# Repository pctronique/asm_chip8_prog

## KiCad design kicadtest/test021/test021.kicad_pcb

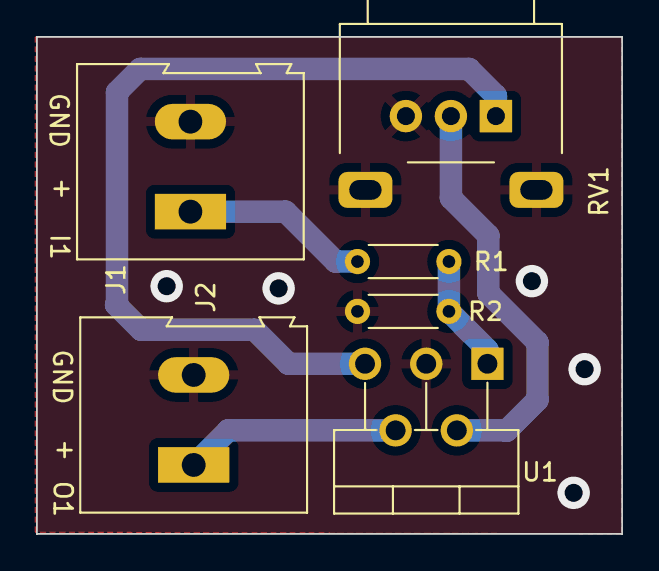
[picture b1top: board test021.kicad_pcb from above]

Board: 2 copper layers, 32.5 x 27.6 mm, 6 parts (0 on the bottom side), 5 nets.

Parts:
J1, J2: TerminalBlock_Altech_AK300-2_P5.00mm
R1, R2: 100k; R_Axial_DIN0204_L3.6mm_D1.6mm_P5.08mm_Horizontal
RV1: 100k; Potentiometer_Alps_RK09L_Single_Horizontal
U1: TO-220-5_P3.4x3.7mm_StaggerOdd_Lead3.8mm_Vertical

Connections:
V1: J1.1, R1.1, RV1.1, U1.5 (V+)
V2: R1.2, R2.1, U1.1 (+)
V3: RV1.2, U1.2 (-)
V4: J2.1, U1.4
VGND: J1.2, J2.2, R2.2, RV1.3, RV1.MP, U1.3 (V-)

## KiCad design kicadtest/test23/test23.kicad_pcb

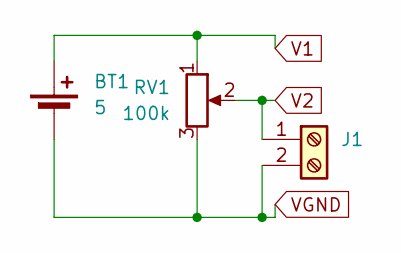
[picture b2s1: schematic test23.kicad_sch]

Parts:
BT1: 5; BatteryHolder_Keystone_103_1x20mm
J1: TerminalBlock_Altech_AK300-2_P5.00mm
RV1: 100k; Potentiometer_Alps_RK09K_Single_Vertical

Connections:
V1: BT1.1 (+), RV1.1
V2: J1.1, RV1.2
VGND: BT1.2 (-), J1.2, RV1.3, RV1.MP

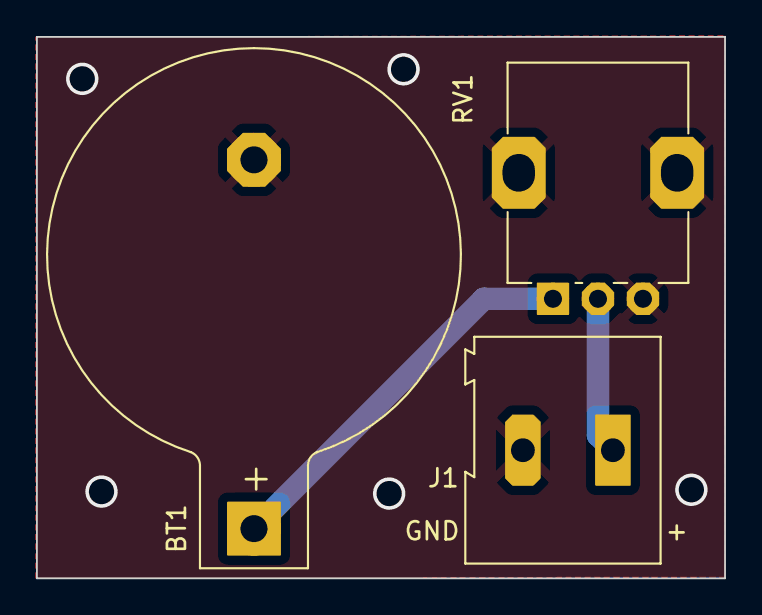
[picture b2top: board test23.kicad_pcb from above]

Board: 2 copper layers, 38.2 x 30.1 mm, 3 parts (0 on the bottom side), 3 nets.

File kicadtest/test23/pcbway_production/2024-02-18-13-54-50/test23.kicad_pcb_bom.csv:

designator,quantity,value,pack,mpn,mount_type
BT1,1,5,BatteryHolder_Keystone_103_1x20mm,,tht
J1,1,~,TerminalBlock_Altech_AK300-2_P5.00mm,,tht
RV1,1,100k,Potentiometer_Alps_RK09K_Single_Vertical,,tht

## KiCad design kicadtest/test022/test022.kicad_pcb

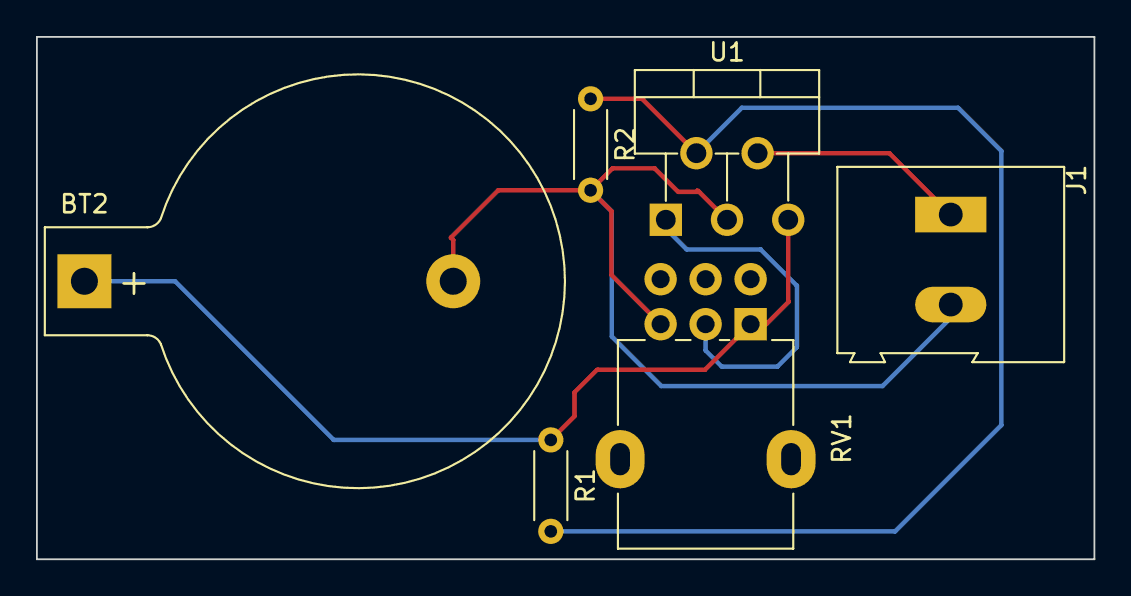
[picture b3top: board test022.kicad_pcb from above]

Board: 2 copper layers, 58.8 x 29.0 mm, 6 parts (0 on the bottom side), 5 nets.

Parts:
BT2: Battery_Cell; BatteryHolder_Keystone_103_1x20mm
J1: Screw_Terminal_01x02; TerminalBlock_Altech_AK300-2_P5.00mm
R1, R2: R; R_Axial_DIN0204_L3.6mm_D1.6mm_P5.08mm_Horizontal
RV1: R_Potentiometer_Dual_Separate; Potentiometer_Alpha_RD902F-40-00D_Dual_Vertical
U1: LM1875; TO-220-5_P3.4x3.7mm_StaggerOdd_Lead3.8mm_Vertical

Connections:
+5V: BT2.1 (+), R1.1, RV1.1, U1.5 (V+)
GND: BT2.2 (-), J1.2, R2.2, RV1.3, U1.3 (V-)
unnamed: J1.1, U1.4
unnamed: RV1.2, U1.1 (+)
unnamed: R1.2, R2.1, U1.2 (-)

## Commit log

2023-09-10 base projet
2024-02-12 add simul
2024-02-12 petite modif
2024-02-13 simul
2024-02-14 image gate
2024-02-14 modif hacheur
2024-02-15 add aop
2024-02-16 modif can cna
2024-02-16 mini modif
2024-02-17 test kicad
2024-02-17 add test23
2024-03-28 modif bug file (00)
2024-04-06 add gitignore
